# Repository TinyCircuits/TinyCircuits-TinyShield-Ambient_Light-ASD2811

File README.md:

# TinyCircuits TinyShield Ambient Light Sensor Board
# ASD2811 Rev2

The design files are located under design_files/ for the TinyCircuits ASD2811 Rev 2 PCB.  This is a TinyShield board (Square Version, 20mm x 20mm, or Circular 20mm diameter) that has a TAOS TSL2572 Ambient Light Sensor, local power supply and level shifters to connect between the TinyDuino and the accelerometer. 

Format is in Cadsoft Eagle format - Eagle version 6.2 was used for the original design.

For more infomation on this, check out the product page at TinyCircuits.com: https://tinycircuits.com/collections/sensors/products/ambient-light-tinyshield

#License:

Design by TinyCircuits.
All design files are released under the Creative Commons Attribution Share-Alike 3.0 License, see the following link for details: http://creativecommons.org/licenses/by-sa/3.0

All text above must be included in any redistribution or derived design

This project uses designs and concepts developed as part of the Arduino project and the LilyPad project.  The TinyCircuits design files themselves (schematics, PCB and libraries) are not directly derived from these works' design files and have been created new, however the concepts and basic architecture behind the TinyDuino and TinyLily products are derived and we thank the hard work of the organizations below for their contributions to open-source hardware:
  
Original Arduino Uno Design by Team Arduino

LilyPad Arduino Design by Leah Buechley and Sparkfun Electronics

Please support the open-source hardware community

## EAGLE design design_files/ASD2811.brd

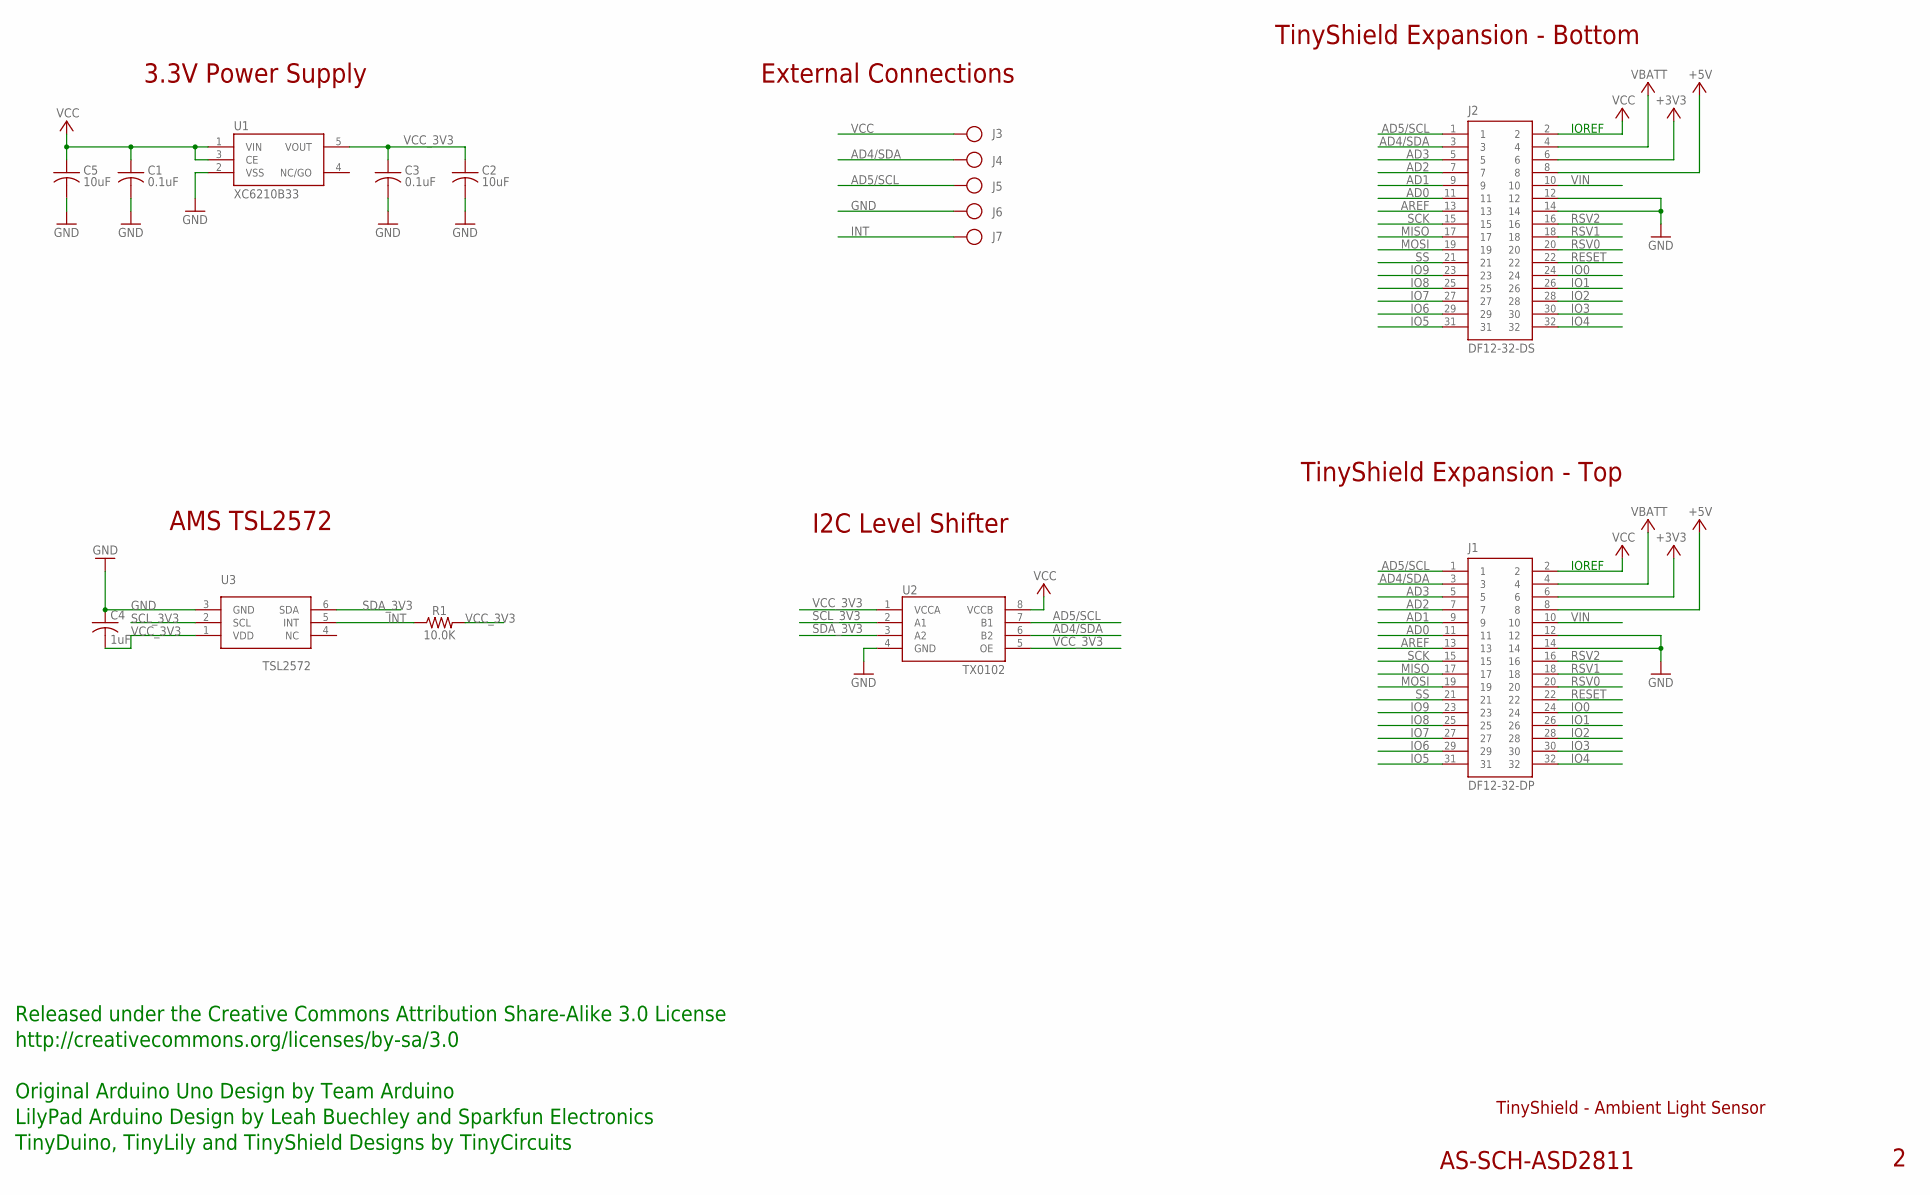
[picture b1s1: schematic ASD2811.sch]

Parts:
C1, C3: 0.1uF; C0402; PARTNO AS-ITM-00008
C2: 10uF; C0805; PARTNO AS-ITM-00045
C4: 1uF; C0402
C5: 10uF; C0805
J1: DF12-32-DP; PARTNO AS-ITM-00015
J2: DF12-32-DS; PARTNO AS-ITM-00012
J3, J4, J5, J6, J7: PIN_1X.1"; 1X.1"
R1: 10.0K; 0402
U1: XC6210B33; SOT-25
U2: TX0102; DQE(R-PX2SON-N8)
U3: TSL2572

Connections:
+3V3: J1.6, J2.6
+5V: J1.8, J2.8
AD0: J1.11, J2.11
AD1: J1.9, J2.9
AD2: J1.7, J2.7
AD3: J1.5, J2.5
AD4/SDA: J1.3, J2.3, J4.1, U2.6 (B2)
AD5/SCL: J1.1, J2.1, J5.1, U2.7 (B1)
AREF: J1.13, J2.13
GND: C1.2, C2.2, C3.2, C4.1, C5.2, J1.12, J1.14, J2.12, J2.14, J6.1, U1.2 (VSS), U2.4 (GND), U3.3 (GND)
INT: J7.1, R1.1, U3.5 (INT)
IO0: J1.24, J2.24
IO1: J1.26, J2.26
IO2: J1.28, J2.28
IO3: J1.30, J2.30
IO4: J1.32, J2.32
IO5: J1.31, J2.31
IO6: J1.29, J2.29
IO7: J1.27, J2.27
IO8: J1.25, J2.25
IO9: J1.23, J2.23
MISO: J1.17, J2.17
MOSI: J1.19, J2.19
RESET: J1.22, J2.22
RSV0: J1.20, J2.20
RSV1: J1.18, J2.18
RSV2: J1.16, J2.16
SCK: J1.15, J2.15
SCL_3V3: U2.2 (A1), U3.2 (SCL)
SDA_3V3: U2.3 (A2), U3.6 (SDA)
SS: J1.21, J2.21
VBATT: J1.4, J2.4
VCC: C1.1, C5.1, J1.2, J2.2, J3.1, U1.1 (VIN), U1.3 (CE), U2.8 (VCCB)
VCC_3V3: C2.1, C3.1, C4.2, R1.2, U1.5 (VOUT), U2.1 (VCCA), U2.5 (OE), U3.1 (VDD)
VIN: J1.10, J2.10

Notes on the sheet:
TinyShield Expansion - Bottom
TinyShield - Ambient Light Sensor
AS-SCH-ASD2811
TinyShield Expansion - Top
IOREF
Released under the Creative Commons Attribution Share-Alike 3.0 License
http://creativecommons.org/licenses/by-sa/3.0
LilyPad Arduino Design by Leah Buechley and Sparkfun Electronics
TinyDuino, TinyLily and TinyShield Designs by TinyCircuits
Original Arduino Uno Design by Team Arduino
External Connections
3.3V Power Supply
I2C Level Shifter
AMS TSL2572

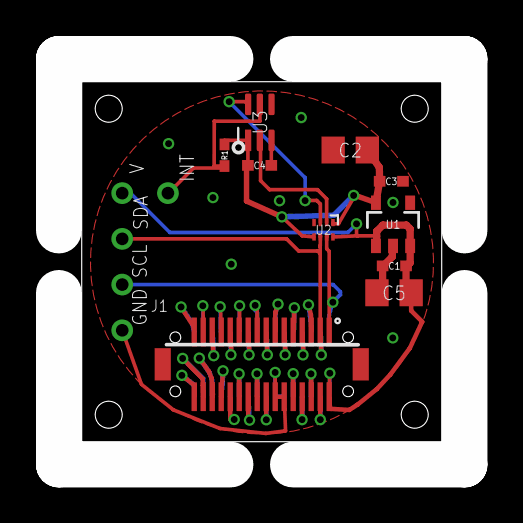
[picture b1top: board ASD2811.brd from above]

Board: 2 copper layers, 20.0 x 20.0 mm, 17 parts (1 on the bottom side), 35 nets.

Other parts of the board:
U$1: DOCFIELD-TINYCIRCUITS-PCB

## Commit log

2014-08-24 Updated Link
2017-03-22 Added example sketch
2017-03-22 Added zip
2019-01-02 Update Rev and format
2019-01-07 updated comments
2019-01-07 updated .zip
2019-01-11 added images
2019-01-11 added serial monitor image
2019-01-11 updated images
2019-02-25 add tutorial images
2020-02-11 image update
2020-03-24 update datasheet
2020-04-13 fix updated program
2020-07-28 Add CAD data
2020-08-14 Update CAD drawing
2020-12-31 updated to use ambient light library
2020-12-31 library fix
